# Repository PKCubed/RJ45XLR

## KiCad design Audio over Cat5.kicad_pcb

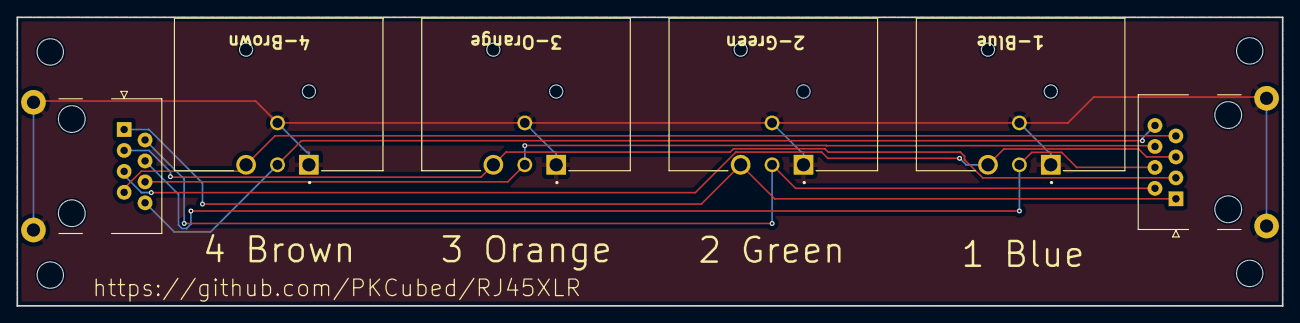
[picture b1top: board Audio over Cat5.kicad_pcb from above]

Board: 2 copper layers, 153.5 x 35.0 mm, 10 parts (0 on the bottom side), 9 nets.

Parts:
H1, H2, H3, H4: MountingHole; MountingHole_3.2mm_M3
J1, J6: RJ45_Shielded; RJ45_HALO_HFJ11-x2450HRL_Horizontal
J7, J8, J9, J10: NC3MAH; NEUTRIK_NC3MAH

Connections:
B: J1.4, J6.4, J7.3
BW: J1.5, J6.5, J7.2
Br: J1.8, J6.8, J10.3
BrW: J1.7, J6.7, J10.2
G: J1.2, J6.2, J8.3
GW: J1.1, J6.1, J8.2
O: J1.6, J6.6, J9.3
OW: J1.3, J6.3, J9.2
SH: J1.SH, J6.SH, J7.1, J7.G, J8.1, J8.G, J9.1, J9.G, J10.1, J10.G

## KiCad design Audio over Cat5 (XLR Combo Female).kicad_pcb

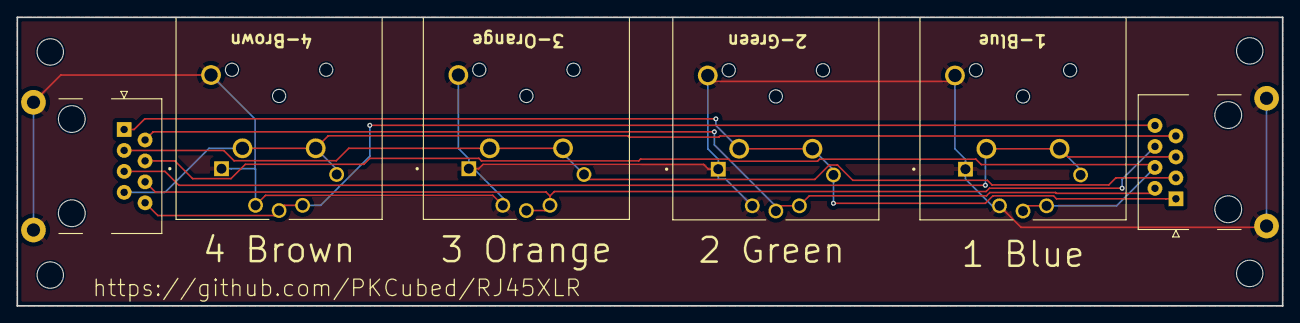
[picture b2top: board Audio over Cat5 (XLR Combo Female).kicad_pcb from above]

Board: 2 copper layers, 153.5 x 35.0 mm, 10 parts (0 on the bottom side), 9 nets.

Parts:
H1, H2, H3, H4: MountingHole; MountingHole_3.2mm_M3
J1, J6: RJ45_Shielded; RJ45_HALO_HFJ11-x2450HRL_Horizontal
J2, J3, J4, J5: NCJ6FA-H; NEUTRIK_NCJ6FA-H

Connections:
B: J1.4, J2.3, J2.R, J6.4
BW: J1.5, J2.2, J2.T1, J2.T2, J6.5
Br: J1.8, J5.3, J5.R, J6.8
BrW: J1.7, J5.2, J5.T1, J5.T2, J6.7
G: J1.2, J3.3, J3.R, J6.2
GW: J1.1, J3.2, J3.T1, J3.T2, J6.1
O: J1.6, J4.3, J4.R, J6.6
OW: J1.3, J4.2, J4.T1, J4.T2, J6.3
SH: J1.SH, J2.1, J2.G, J2.S, J3.1, J3.G, J3.S, J4.1, J4.G, J4.S, J5.1, J5.G, J5.S, J6.SH
